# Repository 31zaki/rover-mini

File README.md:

# rover mini
Welcome to rover-mini Repository!!

This is a self-initiated project designed to explore and learn the full spectrum of engineering from mechanical design and electronics to embedded systems and software development.

<details>
<summary><strong>NOTE for Reviewers and Users</strong></summary>

While I have experience developing hardware as part of a [student-led Mars rover team](https://www.instagram.com/ares_project_official/),
my academic background is originally in Biomedical Engineering.
Fields like robotics, software development, and PCB design are still outside my core expertise.
This project is part of my personal learning journey, and I’m fully aware that there may — or probably should — be mistakes or imperfections.
Any feedback or advice would be warmly appreciated.

Thank you!

</details>

## philosophy
**tiny, but mighty**
  - High performance in not enough; a heart must be woven into the design.
  - More than size — like "山椒は小粒でもぴりりと辛い"
  - Designed with Japanese craftsmanship — tiny in size, vast in spirit.

## features
**manual control**
  - Responsive remote operation using a PlayStation controller via Xbee and Bluetooth communication.
  - Essential for field testing and fine-tuning — offering an intuitive and playful driving experience.

**autonomous**
  - Core functionality designed for the University Rover Challenge Autonomous Mission.
  - Capable of navigating to specified GPS coordinates, detecting ARUCO markers, and identifying mission targets like bottles and hammers.
  - Striving toward true autonomy — small but strategic.

**collaboration with the main rover**
  - Built for intelligent mission sharing: coordinate with the main rover to divide tasks and maximize mission points.
  - Share positional and target information to enhance team efficiency and achieve greater success together.

## hardware overview

This mini rover is designed to be compact yet powerful, with a strong focus on functional performance, manufacturability, and aesthetic design.

### key features:
- High-torque 4WD system capable of navigating tough terrains.
- Rocker mechanism designed with compact miter gears, providing superior maneuverability and articulation.
- Simple and robust fabrication, combining 3D printed parts and laser-cut acrylic plates.
- Two-layer acrylic structure to enhance overall strength and rigidity.
- RealSense depth camera integrated for obstacle avoidance and spatial awareness, supporting advanced path planning.
- Design with a skeleton-like aesthetic, exposing parts of the structure for a visually engaging appearance.
- Soft rubber tyres for excellent traction and smooth handling across various surfaces.
- Dual-computer architecture:
  - Jetson Nano handles computationally intensive tasks like vision processing.
  - Raspberry Pi Pico 2W manages low-level motion control.

### specifications:
- Dimensions: 330 mm (W) × 370 mm (L) × 400 mm (H)
- Weight: 5 kg
- Maximum Speed: 10 m/s
- Power Source: Two 7.2V 4000mAh Ni-MH batteries
- 4-wheel drive system with custom 3D printed inner wheels and rubber tyres

## directory structure (今のところ)
```
```

## system components

| **category**         | **component**                        | **qty** | **details**                                   |
|----------------------|--------------------------------------|---------|-----------------------------------------------|
| **hardware**         | Main Computer                        | 1       | [Jetson Nano 4GB](https://developer.nvidia.com/embedded/learn/get-started-jetson-nano-devkit)|
|                      | Sub Computer                         | 1       | [Raspberry Pi Pico 2 W](https://akizukidenshi.com/catalog/g/g130330/)|
|                      | Battery                              | 2       | [7.2V 4000mAh Ni-MH for Tamiya RC](https://www.amazon.co.jp/-/en/dp/B07789SDYY/?coliid=I2JRBFQTBLRCJF&colid=2I8FL97HRD1KQ&psc=1&ref_=list_c_wl_lv_ov_lig_dp_it) |
|                      | Drive Motor                          | 4       | [100:1 Metal Gearmotor 37Dx73L mm 12V with 64 CPR Encoder (Helical Pinion)](https://www.pololu.com/product/5167) |
|                      | Motor Driver                         | 4       | [TB67H450FNG](https://akizukidenshi.com/catalog/g/g114967/) |
|                      | Tyre                                 | 4       | [5.1 inch RC Crawler Tyre](https://www.amazon.co.jp/dp/B0D9VZH5C3?ref=ppx_yo2ov_dt_b_fed_asin_title)|
|                      | IMU (Inertial Measurement Unit)      | 1       |[BNO055](https://akizukidenshi.com/catalog/g/g116996/) |
|                      | Camera                               | 1       |[Realsense 435i](https://www.intelrealsense.com/depth-camera-d435i/) |
|                      | Indicator                            | 1       |[LED (RGB)](https://www.amazon.co.jp/dp/B09L82BP77?ref=ppx_yo2ov_dt_b_fed_asin_title&th=1) |
|                      | Communication Module                 | 2       |[Xbee](https://www.digi.com/resources/documentation/digidocs/pdfs/90002173.pdf) |
|                      | GPS Module                           | 1       |[Gravity GPS](https://wiki.dfrobot.com/SKU_TEL0157_Gravity_GNSS_Positioning_Module) |
|                      | Emergency Stop Button                | 1       |[KILIGEN 22mm 12-220V 5A](https://www.amazon.co.jp/dp/B0956SRHKC?ref=ppx_yo2ov_dt_b_fed_asin_title&th=1) |
|                      | Miter gear for Rocker Mechanism      | 4       |[M1S25*2310](https://jp.misumi-ec.com/vona2/detail/221000021851/?ProductCode=M1S25*2310)|
|                      | Bearings for Rocker Mechanism        | 6       |[SFL6700ZZ](https://jp.misumi-ec.com/vona2/detail/110302273720/?HissuCode=SFL6700ZZ&PNSearch=SFL6700ZZ&KWSearch=SFL6700ZZ&searchFlow=results2products&list=PageSearchResult)|
|                      | Rocker Shaft Holder                  | 2       |[SSTHIC10M](https://jp.misumi-ec.com/vona2/detail/110300011320/?PNSearch=SSTHIC10M&HissuCode=SSTHIC10M&Keyword=SSTHIC10M&list=SuggestPreview&searchFlow=suggest2products)|
|                      | Wheel Shaft Hub                      | 2       |[AO-8038](https://tamiyashop.jp/shop/g/g89877/)|
| **software**         | Operating System                     || Ubuntu 22.04                                  |
|                      | Programming Framework                || ROS 2 Humble                                    |
|                      | Control Algorithm                    || TBD                                           |
|                      | Communication Protocol               || Wireless communication with the main rover (Xbee) |
| **electronics**      | Please refer to `/Electronics/BOM/`  |||

## Jetson Nano GPIO configuration

| **GPIO pin number**  | **device name**                | **connection (pin or function)**  | **purpose**                     |
|---------------------:|--------------------------------|-----------------------------------|---------------------------------|
| 3 (I2C SDA)          | I2C Bus                        | SDA                               | I2C Data for GPS/BNO055         |
| 5 (I2C SCL)          | I2C Bus                        | SCL                               | I2C Clock for GPS/BNO055        |
| 7                    | LED1                           | LED_1                             | Indicator LED1 Control          |
| 11                   | LED2                           | LED_2                             | Indicator LED2 Control          |
| 13                   | LED3                           | LED_3                             | Indicator LED3 Control          |
| 8 (UART TX)          | Pico RX                        | JETSON_TX-PICO_RX                 | UART Communication              |
| 10 (UART RX)         | Pico TX                        | JETSON_RX-PICO_TX                 | UART Communication              |

## Raspberry Pi pico GPIO configration
| **GPIO pin number** | **device name**                 | **connection (pin or function)**  | **purpose**                     |
|---------------------:|--------------------------------|-----------------------------------|---------------------------------|
| GP0                  | Jetson Nano UART               | JETSON_RX-PICO_TX                 | UART Communication              |
| GP1                  | Jetson Nano UART               | JETSON_TX-PICO_RX                 | UART Communication              |
| GP2                  | Motor Driver LF                | LF_IN1                            | Motor control input             |
| GP3                  | Motor Driver LF                | LF_IN2                            | Motor control input             |
| GP4                  | Motor Driver RF                | RF_IN1                            | Motor control input             |
| GP5                  | Motor Driver RF                | RF_IN2                            | Motor control input             |
| GP6                  | Motor Driver LF                | LF_ENCODER_A                      | Encoder reading                 |
| GP7                  | Motor Driver LF                | LF_ENCODER_B                      | Encoder reading                 |
| GP8                  | Motor Driver RF                | RF_ENCODER_A                      | Encoder reading                 |
| GP9                  | Motor Driver RF                | RF_ENCODER_B                      | Encoder reading                 |
| GP10                 | Motor Driver LR                | LR_IN1                            | Motor control input             |
| GP11                 | Motor Driver LR                | LR_IN2                            | Motor control input             |
| GP12                 | Motor Driver LR                | LR_ENCODER_A                      | Encoder reading                 |
| GP13                 | Motor Driver LR                | LR_ENCODER_B                      | Encoder reading                 |
| GP14                 | Motor Driver RR                | RR_IN1                            | Motor control input             |
| GP15                 | Motor Driver RR                | RR_IN2                            | Motor control input             |
| GP16                 | Motor Driver RR                | RR_ENCODER_A                      | Encoder reading                 |
| GP17                 | Motor Driver RR                | RR_ENCODER_B                      | Encoder reading                 |

LF: Left Front<br>
RF: Right Front<br>
LR: Left Rear<br>
RR: Right Rear<br>

## install required python libraries

## miscellaneous

### project name
The project name "rover-mini" is inspired by the iconic British car [Mini](https://en.wikipedia.org/wiki/Mini). Like its namesake, this rover aims to be compact, functional, and adorable.

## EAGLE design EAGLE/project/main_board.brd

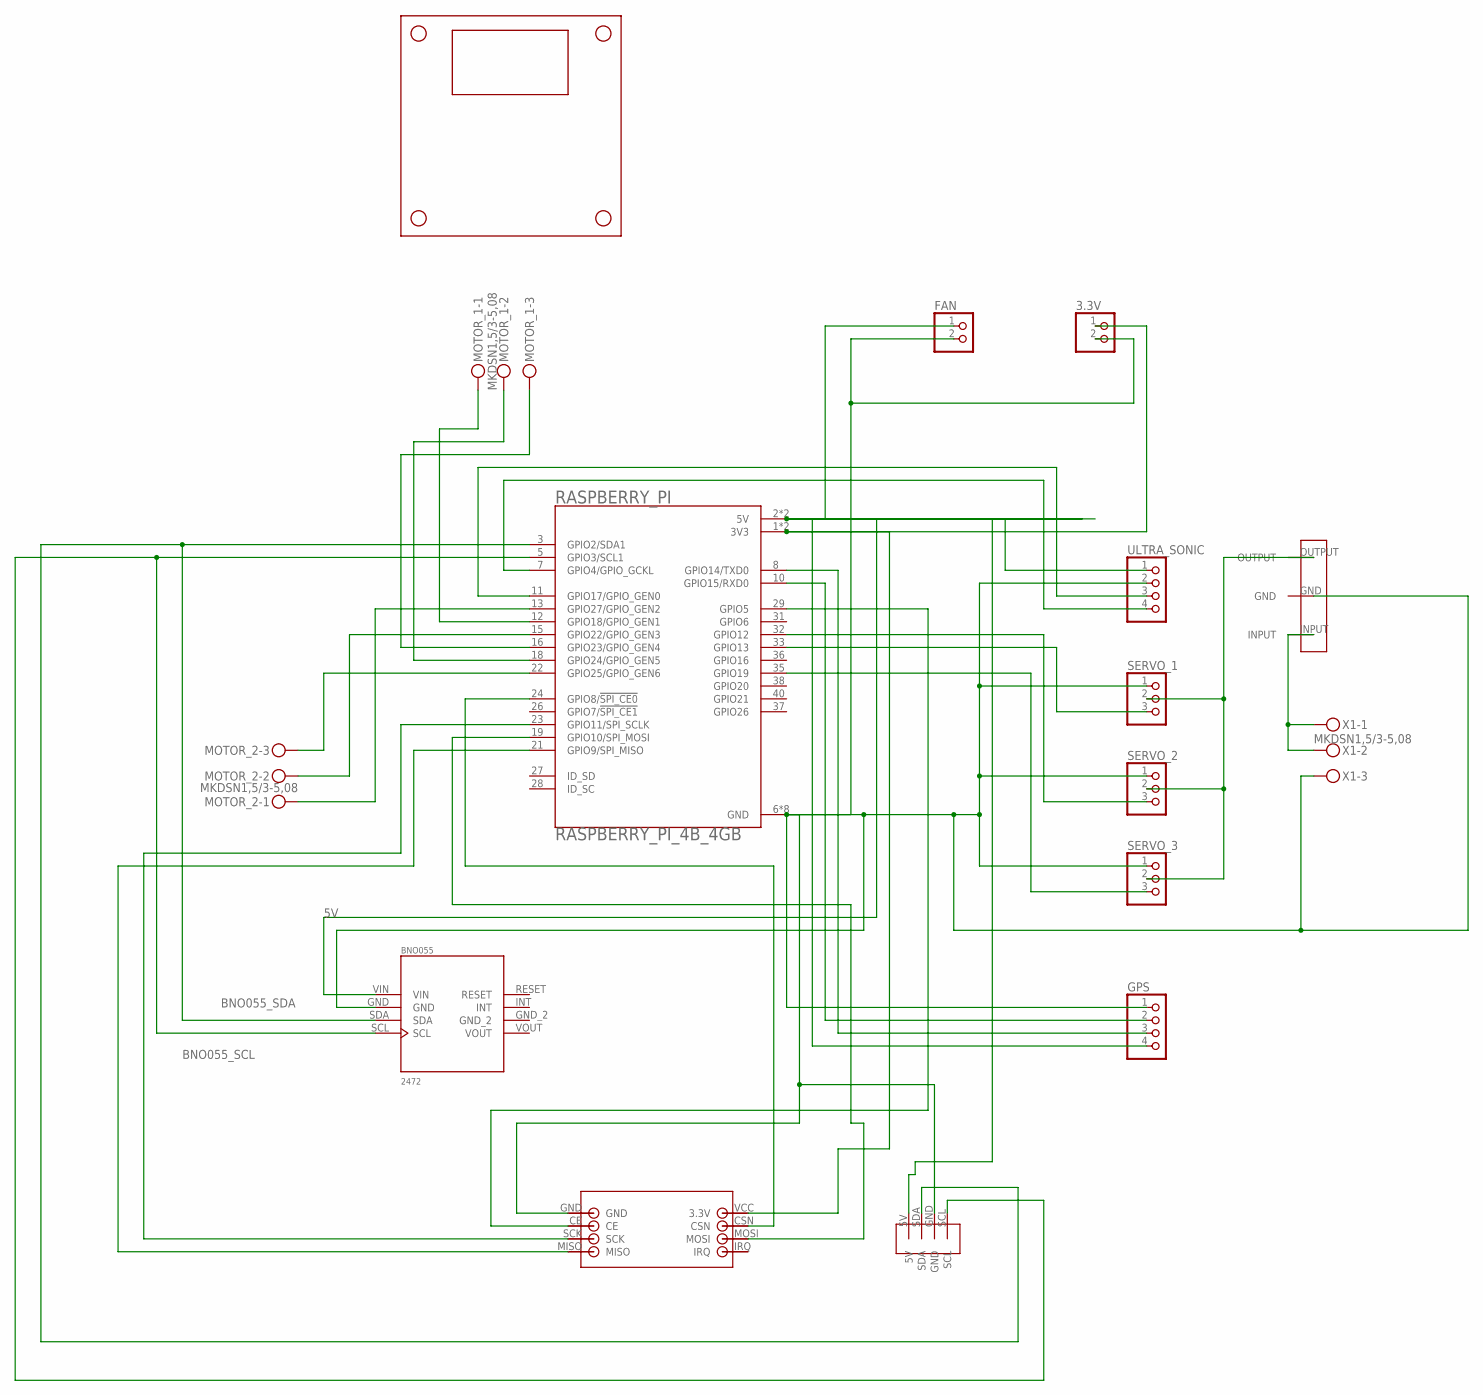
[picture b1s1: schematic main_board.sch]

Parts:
3.3V: PINHD-1X2; 1X02
BNO055: 2472; MODULE_2472
FAN: PINHD-1X2; 1X02
GPS: PINHD-1X4; 1X04
L298N1: L298N_DRIVER
LXDC1: LXDC55
MOTOR_1, MOTOR_2: MKDSN1,5/3-5,08
NRF24L1: NRF24L01
RASPBERRY_PI: RASPBERRY_PI_4B_4GB; MODULE_RASPBERRY_PI_4B_4GB
SERVO_1, SERVO_2, SERVO_3: PINHD-1X3; 1X03
U$1: DHT20
ULTRA_SONIC: PINHD-1X4; 1X04
X1: MKDSN1,5/3-5,08

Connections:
3.3V: 3.3V.1, NRF24L1.VCC (3.3V), RASPBERRY_PI.1 (3V3), RASPBERRY_PI.17 (3V3)
5V: BNO055.VIN, FAN.1, GPS.4, RASPBERRY_PI.2 (5V), RASPBERRY_PI.4 (5V), U$1.5V, ULTRA_SONIC.1
5V_LXDC55: LXDC1.OUTPUT, SERVO_1.2, SERVO_2.2, SERVO_3.2
BATTERY+: LXDC1.INPUT, X1.1, X1.2
BNO055_SCL: BNO055.SCL, RASPBERRY_PI.5 (GPIO3/SCL1), U$1.SCL
BNO055_SDA: BNO055.SDA, RASPBERRY_PI.3 (GPIO2/SDA1), U$1.SDA
CSN: NRF24L1.CSN, RASPBERRY_PI.24 (GPIO8/!SPI_CE0!)
ECHO: RASPBERRY_PI.7 (GPIO4/GPIO_GCKL), ULTRA_SONIC.4
ENA: MOTOR_1.1, RASPBERRY_PI.12 (GPIO18/GPIO_GEN1)
ENB: MOTOR_2.3, RASPBERRY_PI.22 (GPIO25/GPIO_GEN6)
GND: 3.3V.2, BNO055.GND, FAN.2, GPS.1, LXDC1.GND, NRF24L1.GND, RASPBERRY_PI.6 (GND), RASPBERRY_PI.9 (GND), RASPBERRY_PI.14 (GND), RASPBERRY_PI.20 (GND), RASPBERRY_PI.25 (GND), RASPBERRY_PI.30 (GND), RASPBERRY_PI.34 (GND), RASPBERRY_PI.39 (GND), SERVO_1.1, SERVO_2.1, SERVO_3.1, U$1.GND, ULTRA_SONIC.2, X1.3
IN1: MOTOR_1.2, RASPBERRY_PI.18 (GPIO24/GPIO_GEN5)
IN2: MOTOR_1.3, RASPBERRY_PI.16 (GPIO23/GPIO_GEN4)
IN3: MOTOR_2.1, RASPBERRY_PI.13 (GPIO27/GPIO_GEN2)
IN4: MOTOR_2.2, RASPBERRY_PI.15 (GPIO22/GPIO_GEN3)
MISO: NRF24L1.MISO, RASPBERRY_PI.21 (GPIO9/SPI_MISO)
MOSI: NRF24L1.MOSI, RASPBERRY_PI.19 (GPIO10/SPI_MOSI)
NRF_CE_GPIO5: NRF24L1.CE, RASPBERRY_PI.29 (GPIO5)
RX: GPS.3, RASPBERRY_PI.8 (GPIO14/TXD0)
SCK: NRF24L1.SCK, RASPBERRY_PI.23 (GPIO11/SPI_SCLK)
SERVO1_GPIO13: RASPBERRY_PI.33 (GPIO13), SERVO_1.3
SERVO2_GPIO12: RASPBERRY_PI.32 (GPIO12), SERVO_2.3
SERVO3_GPIO19: RASPBERRY_PI.35 (GPIO19), SERVO_3.3
TRIG: RASPBERRY_PI.11 (GPIO17/GPIO_GEN0), ULTRA_SONIC.3
TX: GPS.2, RASPBERRY_PI.10 (GPIO15/RXD0)

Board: 2 copper layers, 16 parts (0 on the bottom side), 25 nets, no tracks yet.

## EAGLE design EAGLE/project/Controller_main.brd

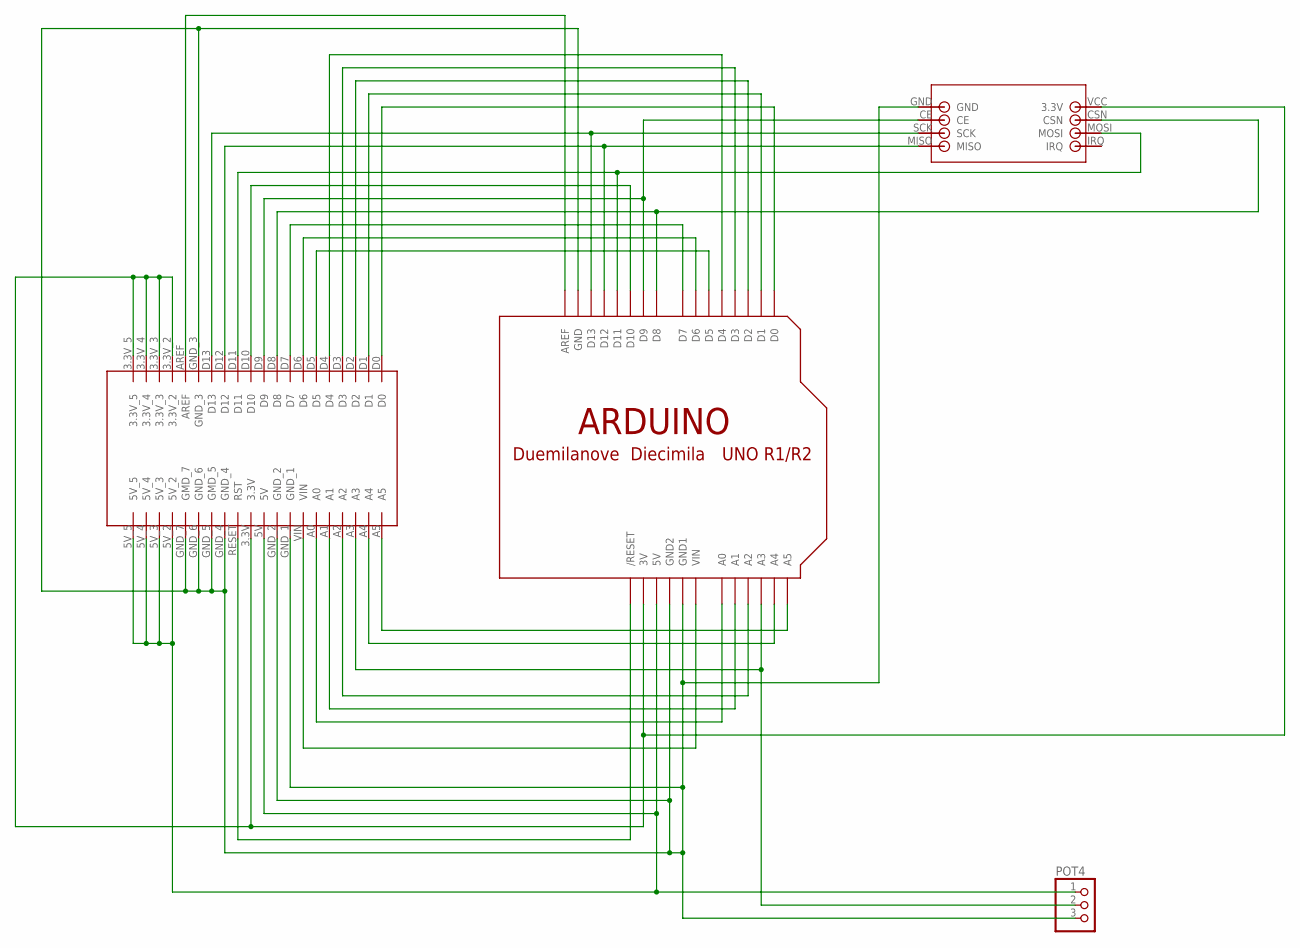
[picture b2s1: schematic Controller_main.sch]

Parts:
2X40CONECTOR1: 2X40_CONNECTOR; 2X40_PIN_CONNECTOR
NRF24L1: NRF24L01
POT4: PINHD-1X3; 1X03
U$1: ARDUINOUNO; ARDUINO

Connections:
3.3V: 2X40CONECTOR1.3.3V, 2X40CONECTOR1.3.3V_2, 2X40CONECTOR1.3.3V_3, 2X40CONECTOR1.3.3V_4, 2X40CONECTOR1.3.3V_5, NRF24L1.VCC (3.3V), U$1.3V
5V: 2X40CONECTOR1.5V, 2X40CONECTOR1.5V_2, 2X40CONECTOR1.5V_3, 2X40CONECTOR1.5V_4, 2X40CONECTOR1.5V_5, POT4.1, U$1.5V
A0: 2X40CONECTOR1.A0, U$1.A0
A1: 2X40CONECTOR1.A1, U$1.A1
A2: 2X40CONECTOR1.A2, U$1.A2
A4: 2X40CONECTOR1.A4, U$1.A4
A5: 2X40CONECTOR1.A5, U$1.A5
AREF: 2X40CONECTOR1.AREF, U$1.AREF
D0: 2X40CONECTOR1.D0, U$1.D0
D1: 2X40CONECTOR1.D1, U$1.D1
D2: 2X40CONECTOR1.D2, U$1.D2
D3: 2X40CONECTOR1.D3, U$1.D3
D4: 2X40CONECTOR1.D4, U$1.D4
D5: 2X40CONECTOR1.D5, U$1.D5
D6: 2X40CONECTOR1.D6, U$1.D6
D7: 2X40CONECTOR1.D7, U$1.D7
D8: 2X40CONECTOR1.D8, NRF24L1.CSN, U$1.D8
D9: 2X40CONECTOR1.D9, NRF24L1.CE, U$1.D9
D10: 2X40CONECTOR1.D10, U$1.D10
D11: 2X40CONECTOR1.D11, NRF24L1.MOSI, U$1.D11
D12: 2X40CONECTOR1.D12, NRF24L1.MISO, U$1.D12
D13: 2X40CONECTOR1.D13, NRF24L1.SCK, U$1.D13
GND: 2X40CONECTOR1.GND_1, 2X40CONECTOR1.GND_2, 2X40CONECTOR1.GND_3, 2X40CONECTOR1.GND_4, 2X40CONECTOR1.GND_5 (GMD_5), 2X40CONECTOR1.GND_6, 2X40CONECTOR1.GND_7 (GMD_7), NRF24L1.GND, POT4.3, U$1.GND, U$1.GND1, U$1.GND2
POT4_A3: 2X40CONECTOR1.A3, POT4.2, U$1.A3
RESET: 2X40CONECTOR1.RESET (RST), U$1.RESET (/RESET)
VIN: 2X40CONECTOR1.VIN, U$1.VIN

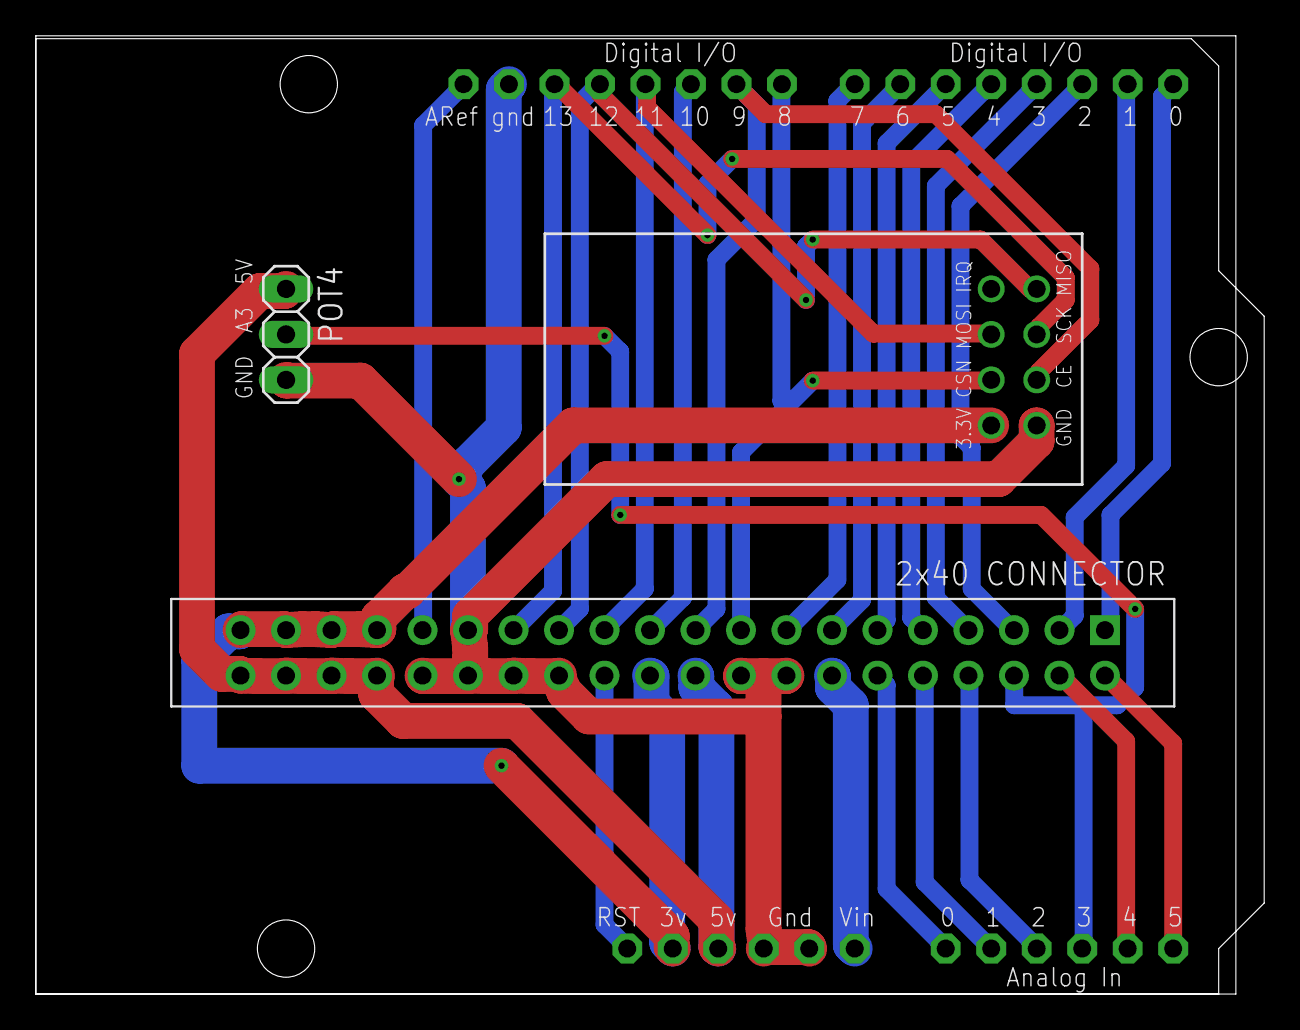
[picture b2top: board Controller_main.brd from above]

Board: 2 copper layers, 68.6 x 53.5 mm, 4 parts (0 on the bottom side), 26 nets.

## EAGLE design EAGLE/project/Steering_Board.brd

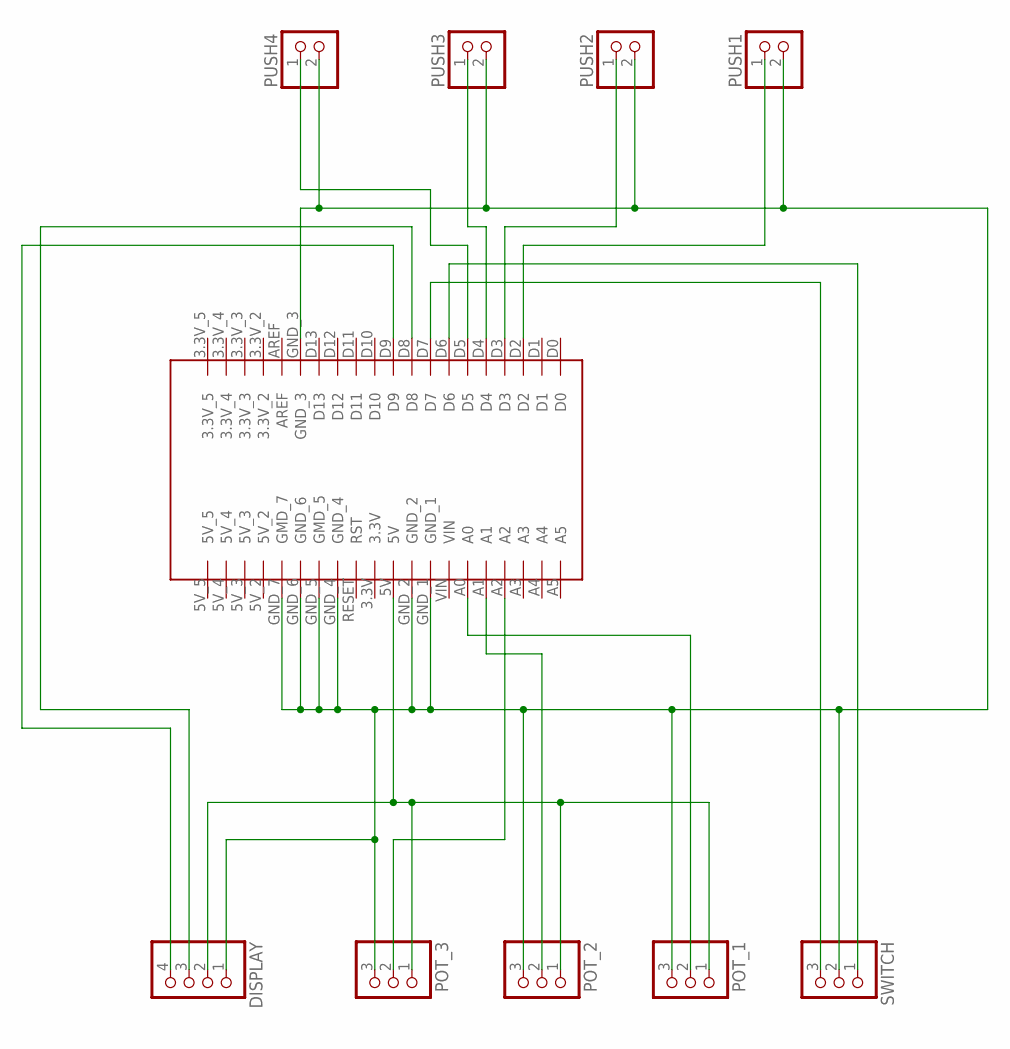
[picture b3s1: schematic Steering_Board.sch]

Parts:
2X40CONECTOR1: 2X40_CONNECTOR; 2X40_PIN_CONNECTOR
DISPLAY: PINHD-1X4; 1X04
POT_1, POT_2, POT_3: PINHD-1X3; 1X03
PUSH1, PUSH2, PUSH3, PUSH4: PINHD-1X2; 1X02
SWITCH: PINHD-1X3; 1X03

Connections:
5V: 2X40CONECTOR1.5V, DISPLAY.2, POT_1.1, POT_2.1, POT_3.1
DISPLAY_D8: 2X40CONECTOR1.D8, DISPLAY.3
DISPLAY_D9: 2X40CONECTOR1.D9, DISPLAY.4
GND: 2X40CONECTOR1.GND_1, 2X40CONECTOR1.GND_2, 2X40CONECTOR1.GND_3, 2X40CONECTOR1.GND_4, 2X40CONECTOR1.GND_5 (GMD_5), 2X40CONECTOR1.GND_6, 2X40CONECTOR1.GND_7 (GMD_7), DISPLAY.1, POT_1.3, POT_2.3, POT_3.3, PUSH1.2, PUSH2.2, PUSH3.2, PUSH4.2, SWITCH.2
POT3_A2: 2X40CONECTOR1.A2, POT_3.2
POTEN1_A0: 2X40CONECTOR1.A0, POT_1.2
POTEN2_A1: 2X40CONECTOR1.A1, POT_2.2
PUSH1_D2: 2X40CONECTOR1.D2, PUSH1.1
PUSH2_D3: 2X40CONECTOR1.D3, PUSH2.1
PUSH3_D4: 2X40CONECTOR1.D4, PUSH3.1
PUSH4_D5: 2X40CONECTOR1.D5, PUSH4.1
SWITCH_D6: 2X40CONECTOR1.D6, SWITCH.1
SWITCH_D7: 2X40CONECTOR1.D7, SWITCH.3

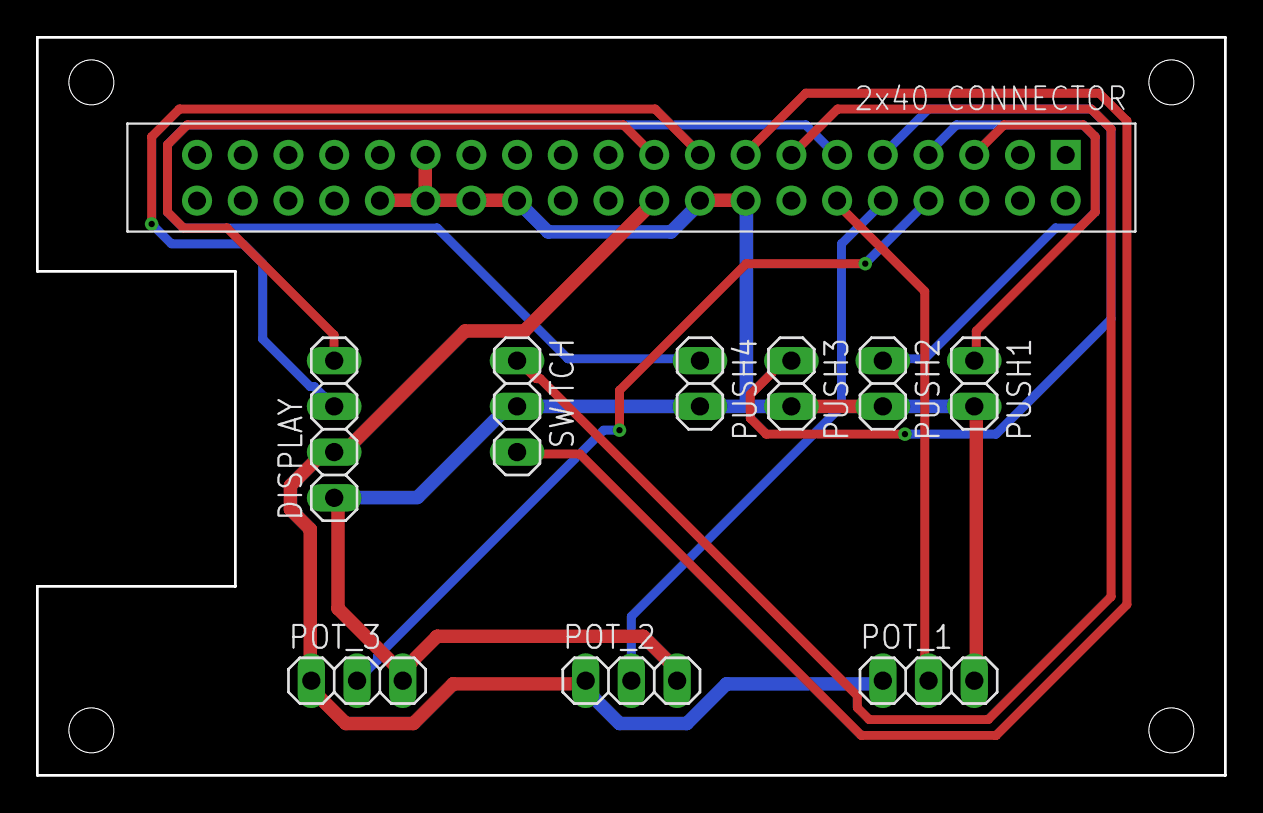
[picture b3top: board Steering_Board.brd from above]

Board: 2 copper layers, 66.0 x 41.0 mm, 10 parts (0 on the bottom side), 13 nets.

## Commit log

2024-07-04 add camera system
2024-07-05 Add ARUCO Tag Detection
2024-07-05 update ARUCO Tag and Face Detection
2024-07-05 update ARUCO tag detection
2024-07-05 Create main_board.s##
2024-07-05 add servo controll
2024-07-06 restore changes
2024-07-06 restore files
2024-07-06 add manual controll
2024-07-06 modify nRF24L01_arduino
2024-07-06 add nRF24L01 files
2024-07-06 changes related to radio communications
2024-07-06 remove
2024-07-07 solve nRF24L01 connection problems
2024-07-07 rename "codes" directory
2024-07-07 update lib_nrf24
2024-07-07 rename directory
2024-07-07 remove Raspi directory
2024-07-07 Create directory for Arduino
2024-07-07 rename a arduino file
2024-07-07 arrange a file of Arduino
2024-07-07 update receive_nRF
2024-07-07 update main board
2024-07-08 Add Steering Wheel brd and sch
2024-07-09 add radio control servo
2024-07-11 use pigpio rather than RPi
2024-07-11 update steering wheel control
2024-07-12 removme unused files
2024-07-14 update servo 1 pin
2025-06-16 First commit and update README.md
2025-06-16 upload 3d models in /hardware
2025-06-17 add image to README.md
2025-07-13 add electronics
2026-05-06 rebuild repository
2026-05-06 add control command
2026-05-08 fix: change baudrate to 9600 for XBee S2C
2026-05-08 fix: rename Software to software (case sensitive)
2026-05-08 feat: add common packet and jetson receiver node
2026-05-11 feat: Add pico firmware
2026-05-11 refactor: clean up teleop directory structure
